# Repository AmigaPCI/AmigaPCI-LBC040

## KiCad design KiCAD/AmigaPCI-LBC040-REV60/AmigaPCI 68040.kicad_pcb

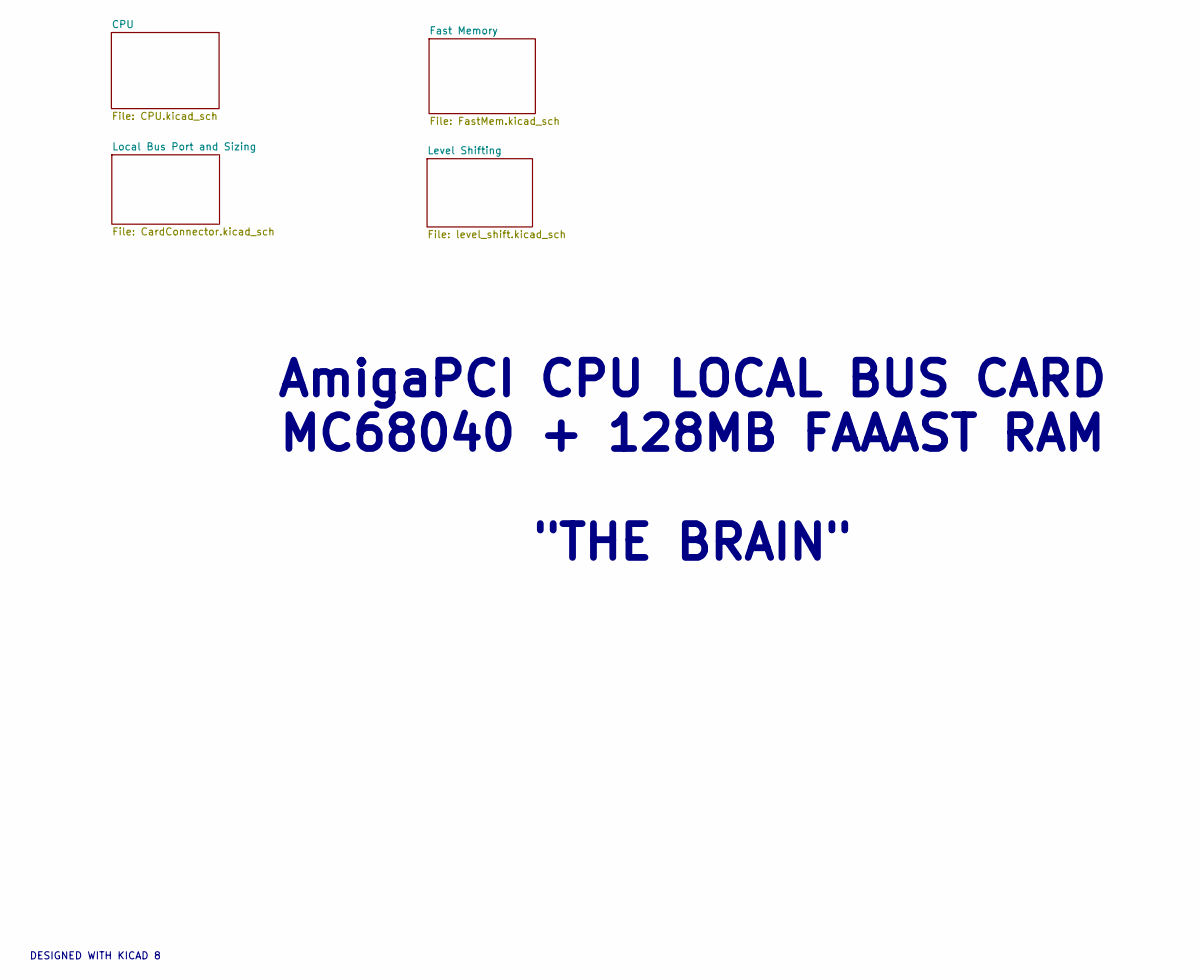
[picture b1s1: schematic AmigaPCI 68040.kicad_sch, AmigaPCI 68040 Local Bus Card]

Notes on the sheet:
DESIGNED WITH KICAD 8
AmigaPCI CPU LOCAL BUS CARD MC68040 + 128MB FAAAST RAM "THE BRAIN"

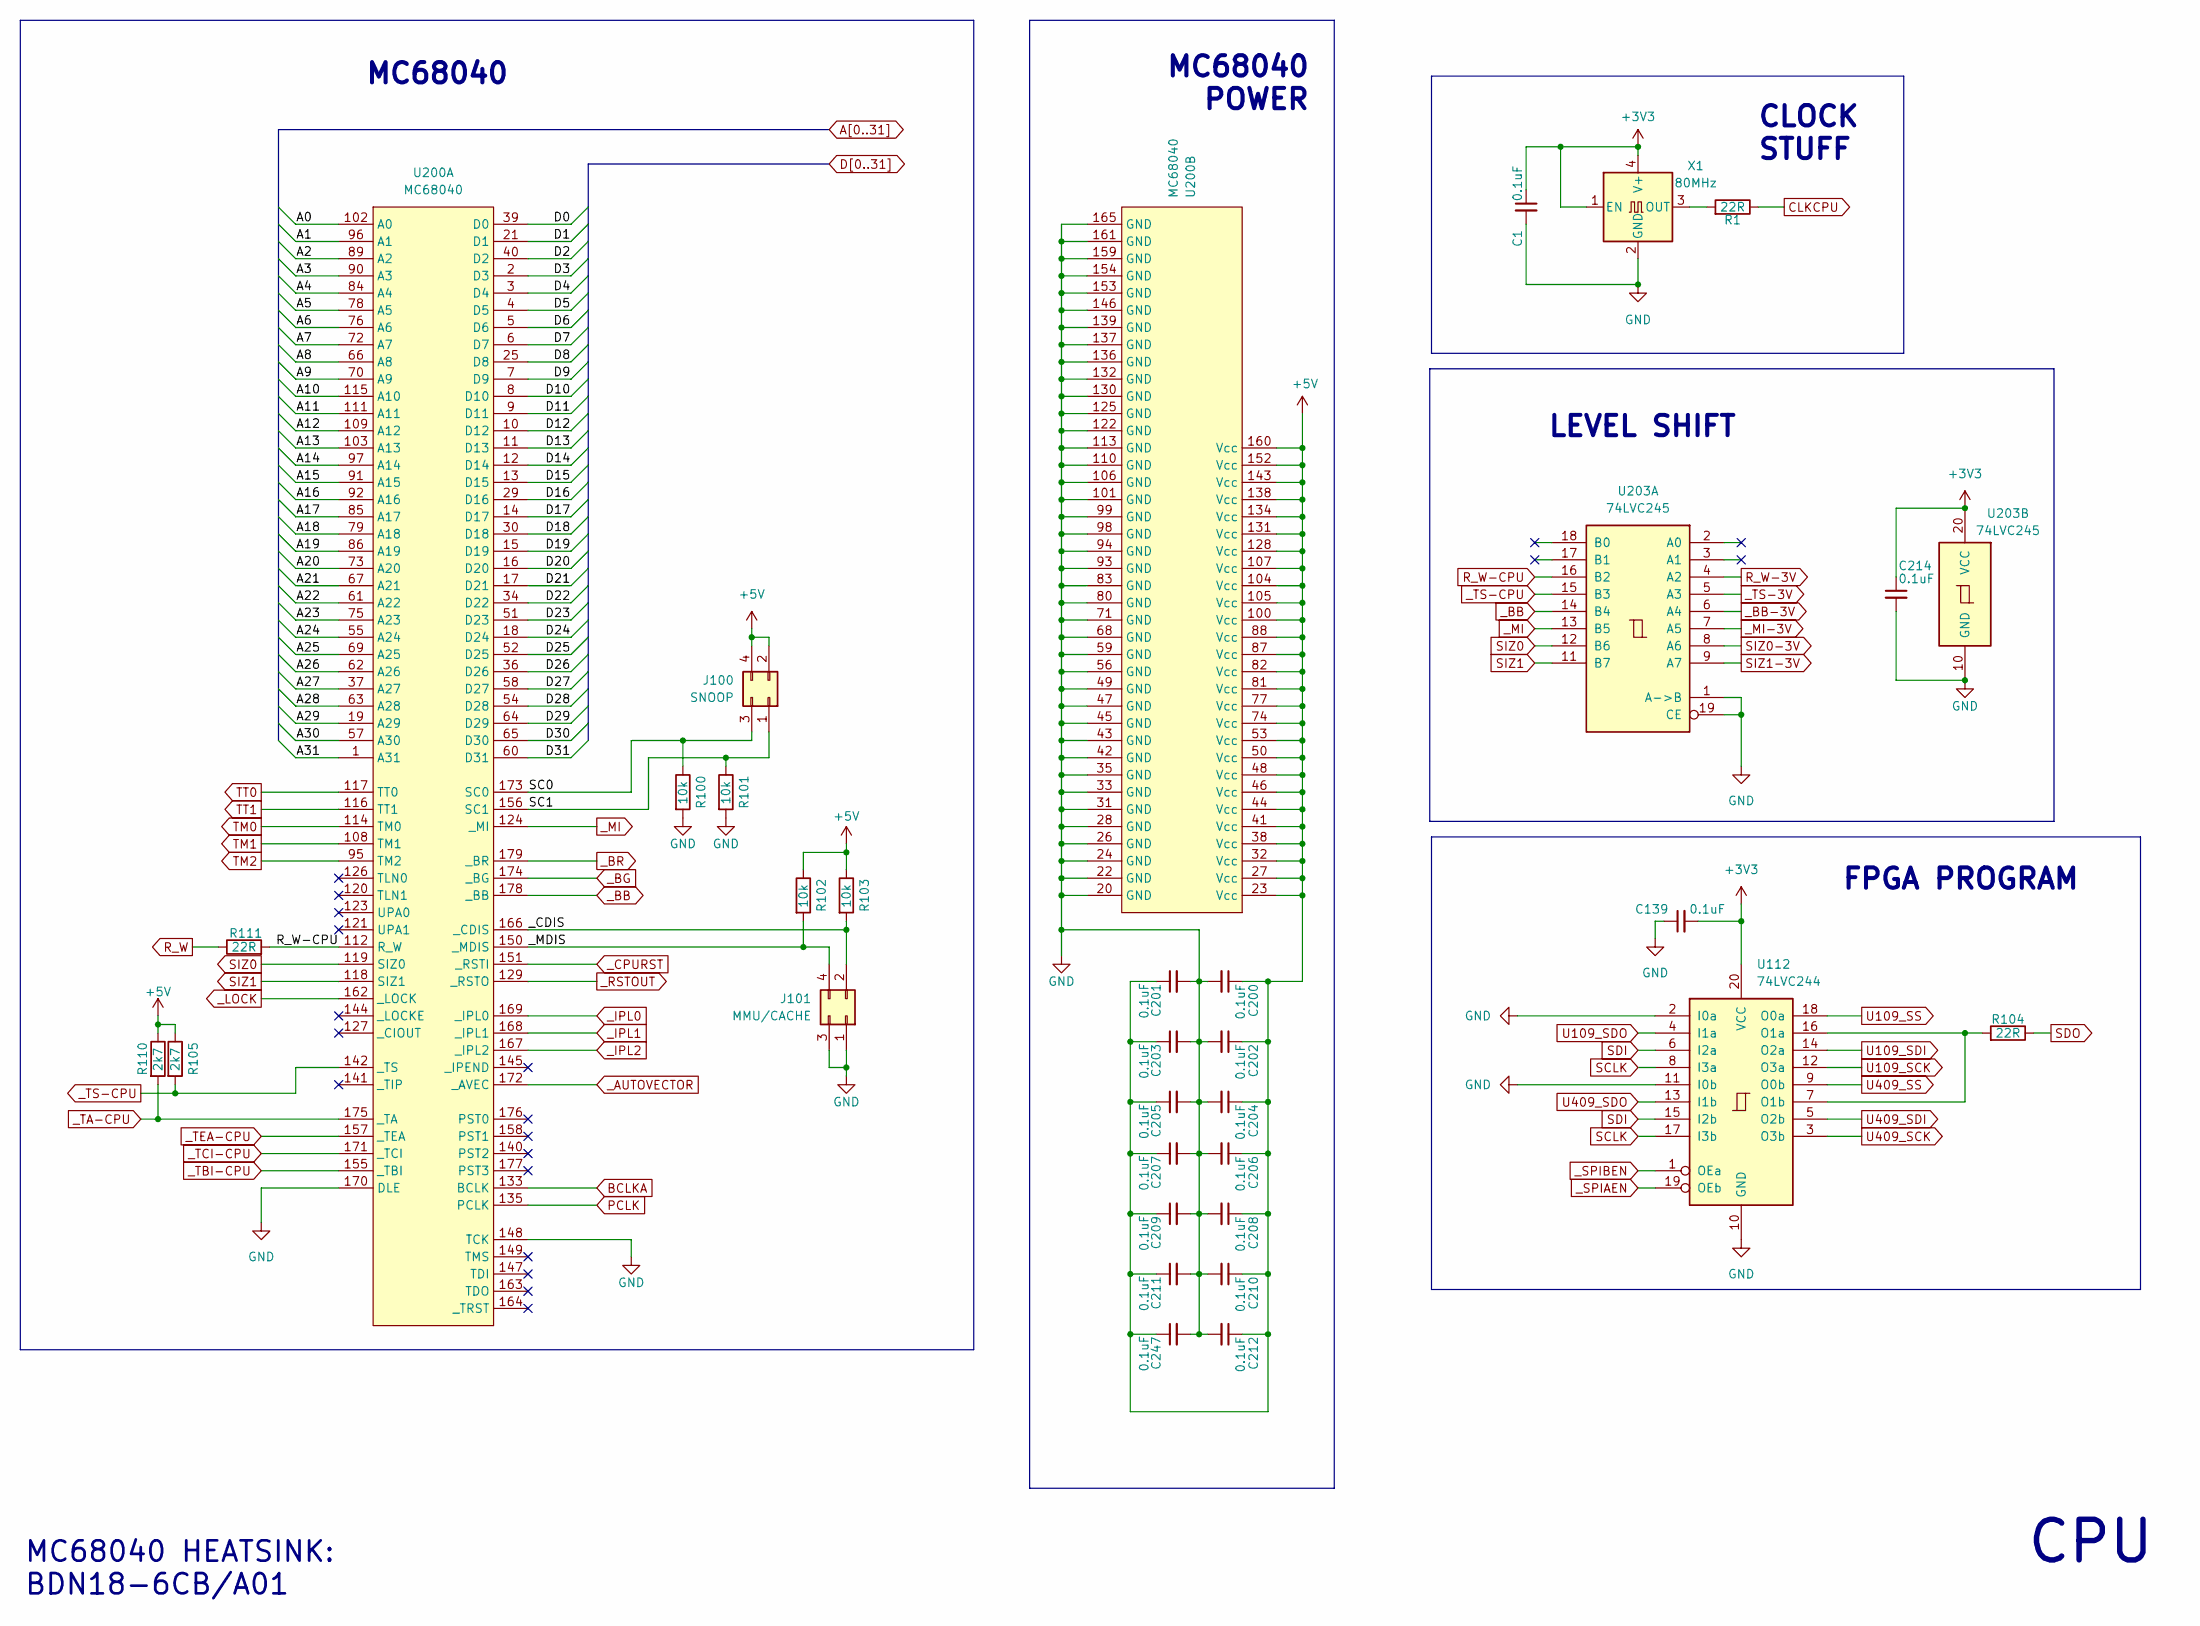
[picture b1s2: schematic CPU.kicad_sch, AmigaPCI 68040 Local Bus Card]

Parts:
C1, C139, C200, C201, C202, C203, C204, C205, C206, C207, C208, C209, C210, C211, C212, C214, C247: 0.1uF; C_0603_1608Metric; LCSC C14663
J100: SNOOP; PinHeader_2x02_P2.54mm_Vertical; LCSC C66690
J101: MMU/CACHE; PinHeader_2x02_P2.54mm_Vertical; LCSC C66690
R1, R104, R111: 22R; R_0603_1608Metric; LCSC C23345
R100, R101, R102, R103: 10k; R_0603_1608Metric; LCSC C25804
R105, R110: 2k7; R_0603_1608Metric; LCSC C13167
U112: 74LVC244; TSSOP-20_4.4x6.5mm_P0.65mm; LCSC C7668
U200: MC68040; PGA179
U203: 74LVC245; TSSOP-20_4.4x6.5mm_P0.65mm; LCSC C7848
X1: 80MHz; Oscillator_SMD_ECS_2520MV-xxx-xx-4Pin_2.5x2.0mm; LCSC C557215

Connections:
+3V3: C1.1, C139.2, C214.1, U112.20 (VCC), U203.20 (VCC), X1.1 (EN), X1.4 (V+); also elsewhere on the board
+5V: C200.1, C201.1, C202.1, C203.1, C204.1, C205.1, C206.1, C207.1, C208.1, C209.1, C210.1, C211.1, C212.1, J100.2, J100.4, R102.1, R103.1, R105.1, R110.1; also elsewhere on the board
/CPU/SC0: J100.3, R100.1; also elsewhere on the board
/CPU/SC1: J100.1, R101.1; also elsewhere on the board
/CPU/_CDIS: J101.2, R103.2; also elsewhere on the board
/CPU/_MDIS: J101.4, R102.2; also elsewhere on the board
GND: C1.2, C139.1, C200.2, C201.2, C202.2, C203.2, C204.2, C205.2, C206.2, C207.2, C208.2, C209.2, C210.2, C211.2, C212.2, C214.2, J101.1, J101.3, R100.2, R101.2, U112.2 (I0a), U112.10 (GND), U112.11 (I0b), U203.1 (A->B), U203.10 (GND), U203.19 (CE), X1.2 (GND); also elsewhere on the board
unnamed: R1.2, X1.3 (OUT)
unnamed: R104.2, U112.7 (O1b), U112.16 (O1a)
R_W: R111.1; also elsewhere on the board
R_W-3V: U203.4 (A2); also elsewhere on the board
R_W-CPU: R111.2, U203.16 (B2); also elsewhere on the board
SCLK: U112.8 (I3a), U112.17 (I3b); also elsewhere on the board
SDI: U112.6 (I2a), U112.15 (I2b); also elsewhere on the board
SDO: R104.1; also elsewhere on the board
SIZ0: U203.12 (B6); also elsewhere on the board
SIZ0-3V: U203.8 (A6); also elsewhere on the board
SIZ1: U203.11 (B7); also elsewhere on the board
SIZ1-3V: U203.9 (A7); also elsewhere on the board
U109_SCK: U112.12 (O3a); also elsewhere on the board
U109_SDI: U112.14 (O2a); also elsewhere on the board
U109_SDO: U112.4 (I1a); also elsewhere on the board
U109_SS: U112.18 (O0a); also elsewhere on the board
U409_SCK: U112.3 (O3b); also elsewhere on the board
U409_SDI: U112.5 (O2b); also elsewhere on the board
U409_SDO: U112.13 (I1b); also elsewhere on the board
U409_SS: U112.9 (O0b); also elsewhere on the board
_BB: U203.14 (B4); also elsewhere on the board
_BB-3V: U203.6 (A4); also elsewhere on the board
_MI: U203.13 (B5); also elsewhere on the board
_MI-3V: U203.7 (A5); also elsewhere on the board
_SPIAEN: U112.19 (OEb); also elsewhere on the board
_SPIBEN: U112.1 (OEa); also elsewhere on the board
_TA-CPU: R110.2; also elsewhere on the board
_TS-3V: U203.5 (A3); also elsewhere on the board
_TS-CPU: R105.2, U203.15 (B3); also elsewhere on the board

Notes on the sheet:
FPGA PROGRAM
MC68040 HEATSINK: BDN18-6CB/A01
LEVEL SHIFT
MC68040
CLOCK STUFF
MC68040 POWER
CPU

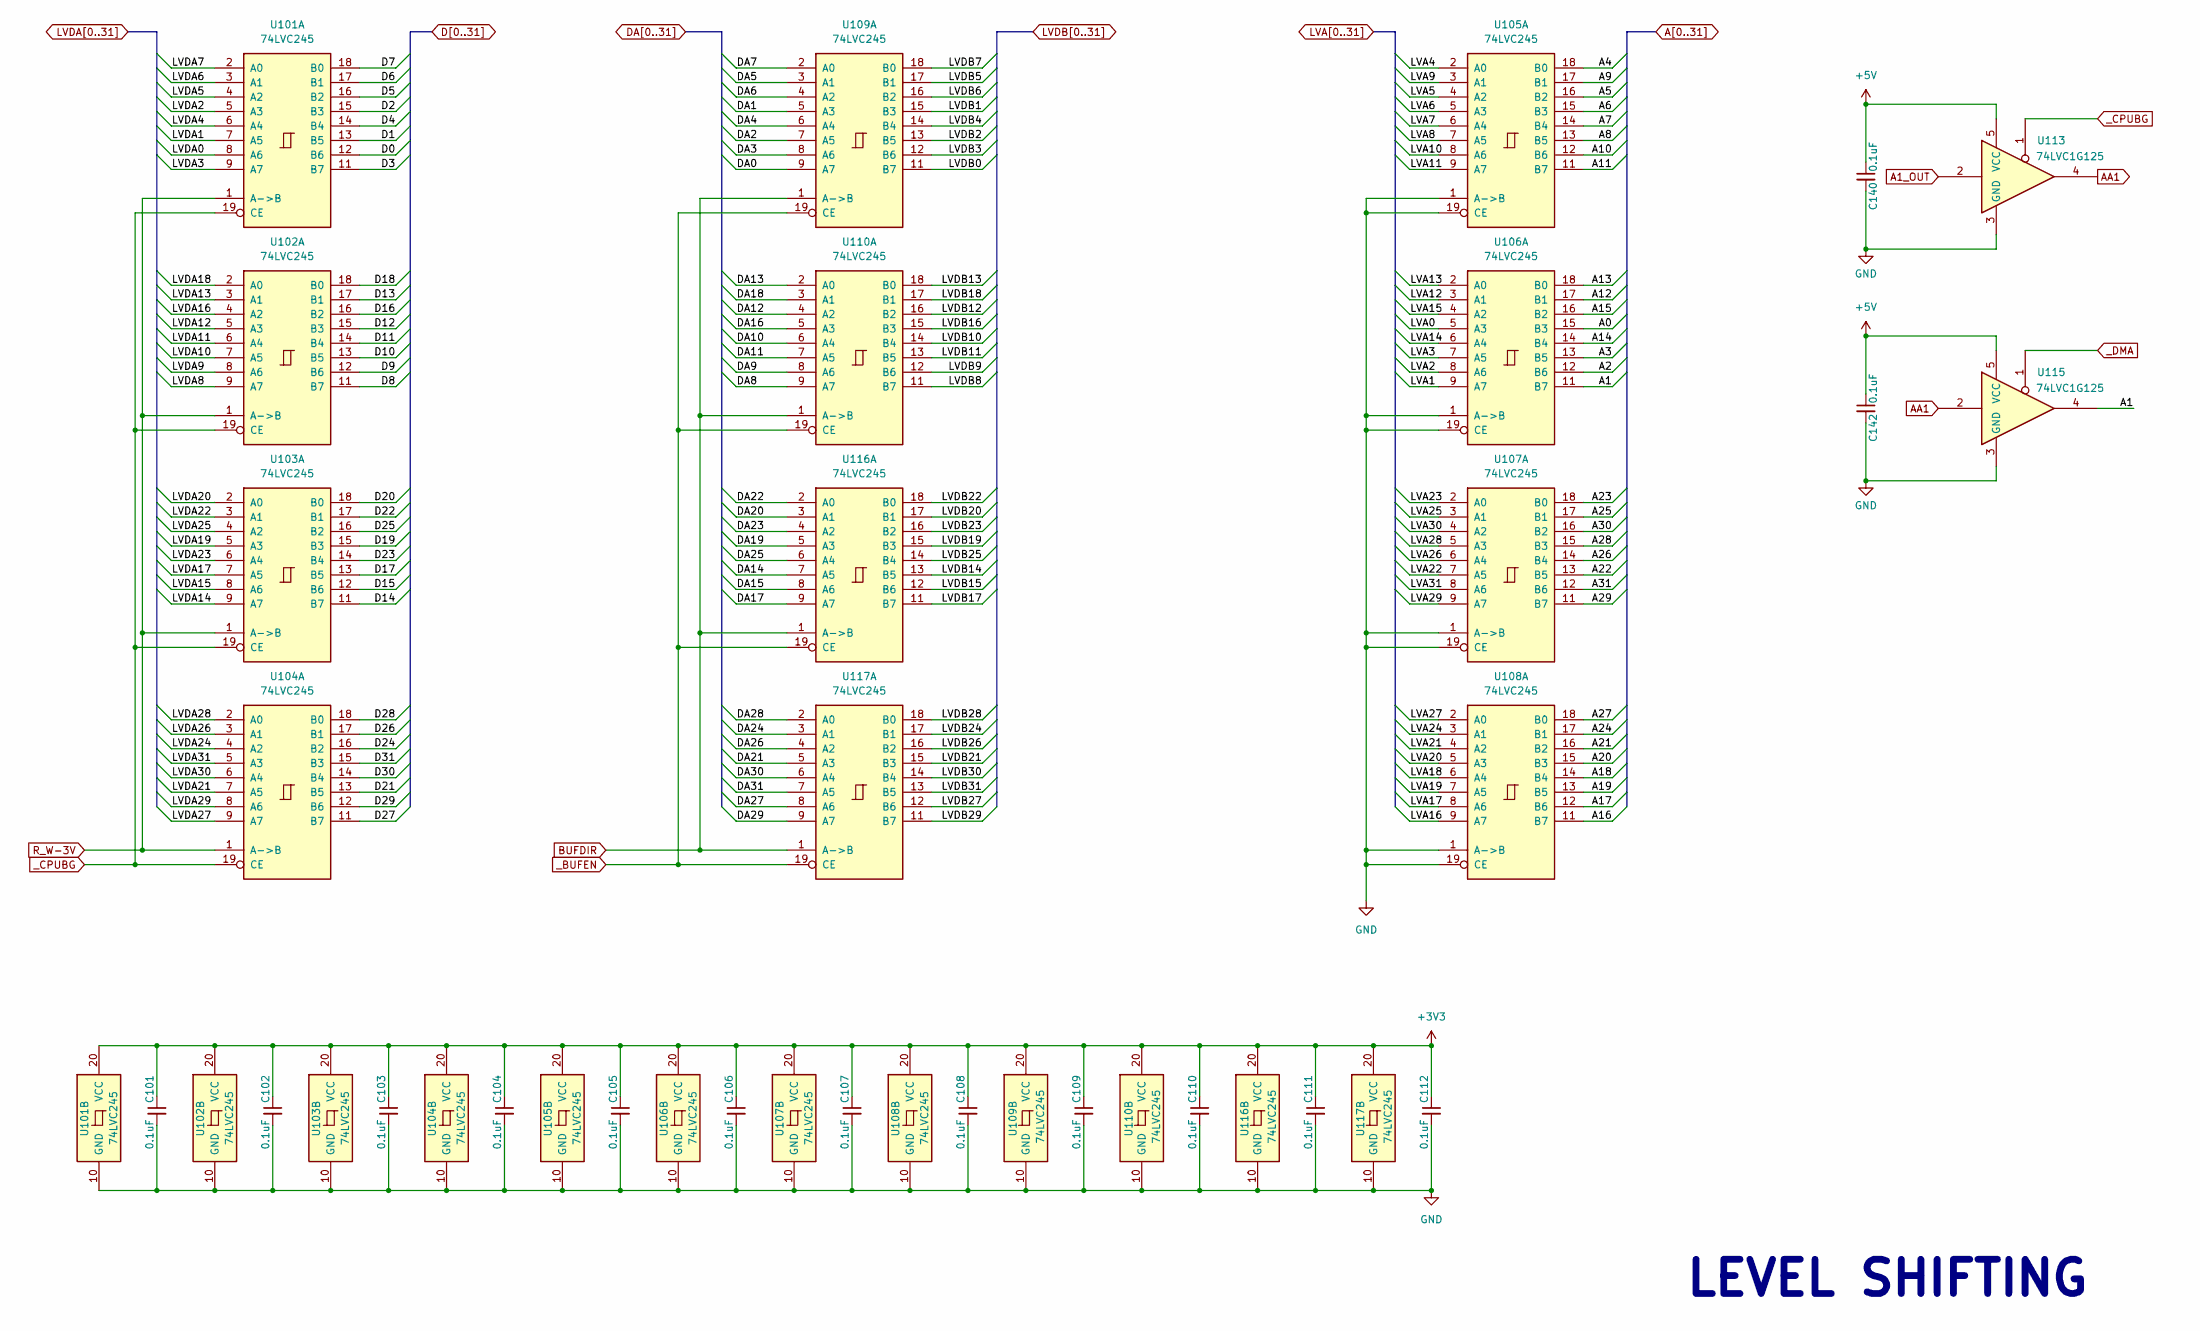
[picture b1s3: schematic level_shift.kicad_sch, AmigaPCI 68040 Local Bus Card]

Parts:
C101, C102, C103, C104, C105, C106, C107, C108, C109, C110, C111, C112, C140, C142: 0.1uF; C_0603_1608Metric; LCSC C14663
U101, U102, U103, U104, U105, U106, U107, U108, U109, U110, U116, U117: 74LVC245; TSSOP-20_4.4x6.5mm_P0.65mm; LCSC C7848
U113, U115: 74LVC1G125; SOT-353_SC-70-5; PartNum SN74LVC1G125DBVR; LCSC C151022

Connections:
+3V3: C101.1, C102.1, C103.1, C104.1, C105.1, C106.1, C107.1, C108.1, C109.1, C110.1, C111.1, C112.1, U101.20 (VCC), U102.20 (VCC), U103.20 (VCC), U104.20 (VCC), U105.20 (VCC), U106.20 (VCC), U107.20 (VCC), U108.20 (VCC), U109.20 (VCC), U110.20 (VCC), U116.20 (VCC), U117.20 (VCC); also elsewhere on the board
+5V: C140.1, C142.1, U113.5 (VCC), U115.5 (VCC); also elsewhere on the board
A0: U106.15 (B3); also elsewhere on the board
A1: U106.11 (B7), U115.4; also elsewhere on the board
A1_OUT: U113.2; also elsewhere on the board
A2: U106.12 (B6); also elsewhere on the board
A3: U106.13 (B5); also elsewhere on the board
A4: U105.18 (B0); also elsewhere on the board
A5: U105.16 (B2); also elsewhere on the board
A6: U105.15 (B3); also elsewhere on the board
A7: U105.14 (B4); also elsewhere on the board
A8: U105.13 (B5); also elsewhere on the board
A9: U105.17 (B1); also elsewhere on the board
A10: U105.12 (B6); also elsewhere on the board
A11: U105.11 (B7); also elsewhere on the board
A12: U106.17 (B1); also elsewhere on the board
A13: U106.18 (B0); also elsewhere on the board
A14: U106.14 (B4); also elsewhere on the board
A15: U106.16 (B2); also elsewhere on the board
A16: U108.11 (B7); also elsewhere on the board
A17: U108.12 (B6); also elsewhere on the board
A18: U108.14 (B4); also elsewhere on the board
A19: U108.13 (B5); also elsewhere on the board
A20: U108.15 (B3); also elsewhere on the board
A21: U108.16 (B2); also elsewhere on the board
A22: U107.13 (B5); also elsewhere on the board
A23: U107.18 (B0); also elsewhere on the board
A24: U108.17 (B1); also elsewhere on the board
A25: U107.17 (B1); also elsewhere on the board
A26: U107.14 (B4); also elsewhere on the board
A27: U108.18 (B0); also elsewhere on the board
A28: U107.15 (B3); also elsewhere on the board
A29: U107.11 (B7); also elsewhere on the board
A30: U107.16 (B2); also elsewhere on the board
A31: U107.12 (B6); also elsewhere on the board
AA1: U113.4, U115.2; also elsewhere on the board
BUFDIR: U109.1 (A->B), U110.1 (A->B), U116.1 (A->B), U117.1 (A->B); also elsewhere on the board
D0: U101.12 (B6); also elsewhere on the board
D1: U101.13 (B5); also elsewhere on the board
D2: U101.15 (B3); also elsewhere on the board
D3: U101.11 (B7); also elsewhere on the board
D4: U101.14 (B4); also elsewhere on the board
D5: U101.16 (B2); also elsewhere on the board
D6: U101.17 (B1); also elsewhere on the board
D7: U101.18 (B0); also elsewhere on the board
D8: U102.11 (B7); also elsewhere on the board
D9: U102.12 (B6); also elsewhere on the board
D10: U102.13 (B5); also elsewhere on the board
D11: U102.14 (B4); also elsewhere on the board
D12: U102.15 (B3); also elsewhere on the board
D13: U102.17 (B1); also elsewhere on the board
D14: U103.11 (B7); also elsewhere on the board
D15: U103.12 (B6); also elsewhere on the board
D16: U102.16 (B2); also elsewhere on the board
D17: U103.13 (B5); also elsewhere on the board
D18: U102.18 (B0); also elsewhere on the board
D19: U103.15 (B3); also elsewhere on the board
D20: U103.18 (B0); also elsewhere on the board
D21: U104.13 (B5); also elsewhere on the board
D22: U103.17 (B1); also elsewhere on the board
D23: U103.14 (B4); also elsewhere on the board
D24: U104.16 (B2); also elsewhere on the board
D25: U103.16 (B2); also elsewhere on the board
D26: U104.17 (B1); also elsewhere on the board
D27: U104.11 (B7); also elsewhere on the board
D28: U104.18 (B0); also elsewhere on the board
D29: U104.12 (B6); also elsewhere on the board
D30: U104.14 (B4); also elsewhere on the board
D31: U104.15 (B3); also elsewhere on the board
DA0: U109.9 (A7); also elsewhere on the board
DA1: U109.5 (A3); also elsewhere on the board
DA2: U109.7 (A5); also elsewhere on the board
DA3: U109.8 (A6); also elsewhere on the board
DA4: U109.6 (A4); also elsewhere on the board
DA5: U109.3 (A1); also elsewhere on the board
DA6: U109.4 (A2); also elsewhere on the board
DA7: U109.2 (A0); also elsewhere on the board
DA8: U110.9 (A7); also elsewhere on the board
DA9: U110.8 (A6); also elsewhere on the board
DA10: U110.6 (A4); also elsewhere on the board
DA11: U110.7 (A5); also elsewhere on the board
DA12: U110.4 (A2); also elsewhere on the board
DA13: U110.2 (A0); also elsewhere on the board
DA14: U116.7 (A5); also elsewhere on the board
DA15: U116.8 (A6); also elsewhere on the board
DA16: U110.5 (A3); also elsewhere on the board
DA17: U116.9 (A7); also elsewhere on the board
DA18: U110.3 (A1); also elsewhere on the board
DA19: U116.5 (A3); also elsewhere on the board
DA20: U116.3 (A1); also elsewhere on the board
DA21: U117.5 (A3); also elsewhere on the board
DA22: U116.2 (A0); also elsewhere on the board
DA23: U116.4 (A2); also elsewhere on the board
DA24: U117.3 (A1); also elsewhere on the board
DA25: U116.6 (A4); also elsewhere on the board
DA26: U117.4 (A2); also elsewhere on the board
DA27: U117.8 (A6); also elsewhere on the board
DA28: U117.2 (A0); also elsewhere on the board
DA29: U117.9 (A7); also elsewhere on the board
DA30: U117.6 (A4); also elsewhere on the board
DA31: U117.7 (A5); also elsewhere on the board
GND: C101.2, C102.2, C103.2, C104.2, C105.2, C106.2, C107.2, C108.2, C109.2, C110.2, C111.2, C112.2, C140.2, C142.2, U101.10 (GND), U102.10 (GND), U103.10 (GND), U104.10 (GND), U105.1 (A->B), U105.10 (GND), U105.19 (CE), U106.1 (A->B), U106.10 (GND), U106.19 (CE), U107.1 (A->B), U107.10 (GND), U107.19 (CE), U108.1 (A->B), U108.10 (GND), U108.19 (CE), U109.10 (GND), U110.10 (GND), U113.3 (GND), U115.3 (GND), U116.10 (GND), U117.10 (GND); also elsewhere on the board
LVA0: U106.5 (A3); also elsewhere on the board
LVA1: U106.9 (A7); also elsewhere on the board
LVA2: U106.8 (A6); also elsewhere on the board
LVA3: U106.7 (A5); also elsewhere on the board
LVA4: U105.2 (A0); also elsewhere on the board
LVA5: U105.4 (A2); also elsewhere on the board
LVA6: U105.5 (A3); also elsewhere on the board
LVA7: U105.6 (A4); also elsewhere on the board
LVA8: U105.7 (A5); also elsewhere on the board
LVA9: U105.3 (A1); also elsewhere on the board
LVA10: U105.8 (A6); also elsewhere on the board
LVA11: U105.9 (A7); also elsewhere on the board
LVA12: U106.3 (A1); also elsewhere on the board
LVA13: U106.2 (A0); also elsewhere on the board
LVA14: U106.6 (A4); also elsewhere on the board
LVA15: U106.4 (A2); also elsewhere on the board
LVA16: U108.9 (A7); also elsewhere on the board
LVA17: U108.8 (A6); also elsewhere on the board
LVA18: U108.6 (A4); also elsewhere on the board
LVA19: U108.7 (A5); also elsewhere on the board
LVA20: U108.5 (A3); also elsewhere on the board
LVA21: U108.4 (A2); also elsewhere on the board
LVA22: U107.7 (A5); also elsewhere on the board
LVA23: U107.2 (A0); also elsewhere on the board
LVA24: U108.3 (A1); also elsewhere on the board
LVA25: U107.3 (A1); also elsewhere on the board
LVA26: U107.6 (A4); also elsewhere on the board
LVA27: U108.2 (A0); also elsewhere on the board
LVA28: U107.5 (A3); also elsewhere on the board
LVA29: U107.9 (A7); also elsewhere on the board
LVA30: U107.4 (A2); also elsewhere on the board
LVA31: U107.8 (A6); also elsewhere on the board
LVDA0: U101.8 (A6); also elsewhere on the board
LVDA1: U101.7 (A5); also elsewhere on the board
LVDA2: U101.5 (A3); also elsewhere on the board
LVDA3: U101.9 (A7); also elsewhere on the board
LVDA4: U101.6 (A4); also elsewhere on the board
LVDA5: U101.4 (A2); also elsewhere on the board
LVDA6: U101.3 (A1); also elsewhere on the board
LVDA7: U101.2 (A0); also elsewhere on the board
LVDA8: U102.9 (A7); also elsewhere on the board
LVDA9: U102.8 (A6); also elsewhere on the board
LVDA10: U102.7 (A5); also elsewhere on the board
LVDA11: U102.6 (A4); also elsewhere on the board
LVDA12: U102.5 (A3); also elsewhere on the board
LVDA13: U102.3 (A1); also elsewhere on the board
LVDA14: U103.9 (A7); also elsewhere on the board
LVDA15: U103.8 (A6); also elsewhere on the board
LVDA16: U102.4 (A2); also elsewhere on the board
LVDA17: U103.7 (A5); also elsewhere on the board
LVDA18: U102.2 (A0); also elsewhere on the board
LVDA19: U103.5 (A3); also elsewhere on the board
LVDA20: U103.2 (A0); also elsewhere on the board
LVDA21: U104.7 (A5); also elsewhere on the board
LVDA22: U103.3 (A1); also elsewhere on the board
LVDA23: U103.6 (A4); also elsewhere on the board
LVDA24: U104.4 (A2); also elsewhere on the board
LVDA25: U103.4 (A2); also elsewhere on the board
LVDA26: U104.3 (A1); also elsewhere on the board
LVDA27: U104.9 (A7); also elsewhere on the board
LVDA28: U104.2 (A0); also elsewhere on the board
LVDA29: U104.8 (A6); also elsewhere on the board
LVDA30: U104.6 (A4); also elsewhere on the board
LVDA31: U104.5 (A3); also elsewhere on the board
LVDB0: U109.11 (B7); also elsewhere on the board
LVDB1: U109.15 (B3); also elsewhere on the board
LVDB2: U109.13 (B5); also elsewhere on the board
LVDB3: U109.12 (B6); also elsewhere on the board
LVDB4: U109.14 (B4); also elsewhere on the board
LVDB5: U109.17 (B1); also elsewhere on the board
LVDB6: U109.16 (B2); also elsewhere on the board
LVDB7: U109.18 (B0); also elsewhere on the board
LVDB8: U110.11 (B7); also elsewhere on the board
LVDB9: U110.12 (B6); also elsewhere on the board
LVDB10: U110.14 (B4); also elsewhere on the board
LVDB11: U110.13 (B5); also elsewhere on the board
LVDB12: U110.16 (B2); also elsewhere on the board
LVDB13: U110.18 (B0); also elsewhere on the board
LVDB14: U116.13 (B5); also elsewhere on the board
LVDB15: U116.12 (B6); also elsewhere on the board
LVDB16: U110.15 (B3); also elsewhere on the board
LVDB17: U116.11 (B7); also elsewhere on the board
LVDB18: U110.17 (B1); also elsewhere on the board
LVDB19: U116.15 (B3); also elsewhere on the board
LVDB20: U116.17 (B1); also elsewhere on the board
LVDB21: U117.15 (B3); also elsewhere on the board
LVDB22: U116.18 (B0); also elsewhere on the board
LVDB23: U116.16 (B2); also elsewhere on the board
LVDB24: U117.17 (B1); also elsewhere on the board
LVDB25: U116.14 (B4); also elsewhere on the board
LVDB26: U117.16 (B2); also elsewhere on the board
LVDB27: U117.12 (B6); also elsewhere on the board
LVDB28: U117.18 (B0); also elsewhere on the board
LVDB29: U117.11 (B7); also elsewhere on the board
LVDB30: U117.14 (B4); also elsewhere on the board
LVDB31: U117.13 (B5); also elsewhere on the board
R_W-3V: U101.1 (A->B), U102.1 (A->B), U103.1 (A->B), U104.1 (A->B); also elsewhere on the board
_BUFEN: U109.19 (CE), U110.19 (CE), U116.19 (CE), U117.19 (CE); also elsewhere on the board
_CPUBG: U101.19 (CE), U102.19 (CE), U103.19 (CE), U104.19 (CE), U113.1; also elsewhere on the board
_DMA: U115.1; also elsewhere on the board

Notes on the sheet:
LEVEL SHIFTING
